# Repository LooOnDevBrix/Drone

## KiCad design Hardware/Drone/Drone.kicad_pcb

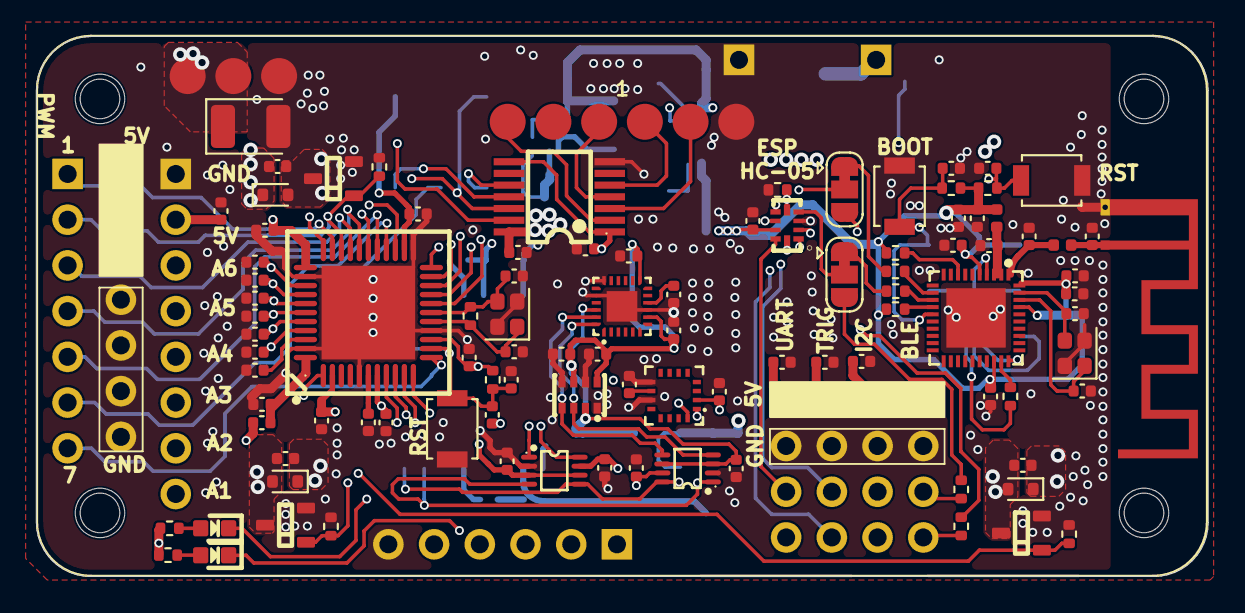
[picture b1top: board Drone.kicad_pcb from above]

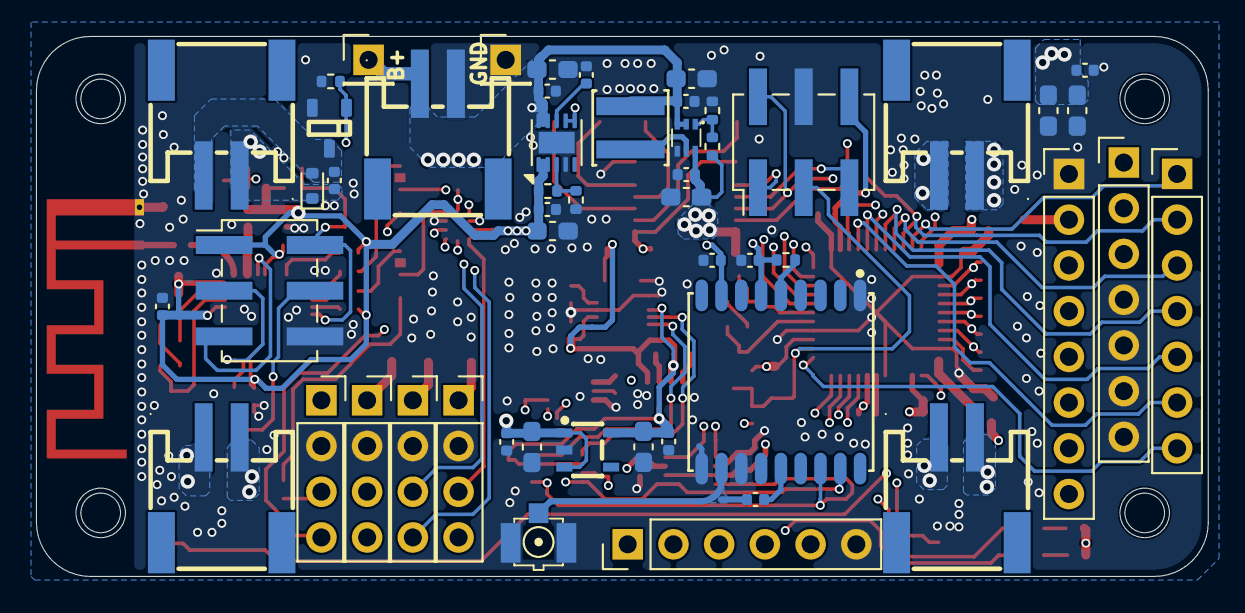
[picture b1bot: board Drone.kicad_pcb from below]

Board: 4 copper layers, 65.1 x 30.0 mm, 164 parts (52 on the bottom side), 85 nets.

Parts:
A1: RASPBERRYPI-ZERO; RASPBERRYPI-ZERO_RPI-ZERO
C1, C2, C18, C22, C26, C29, C32, C34: 10uF; C_0603_1608Metric_Pad1.08x0.95mm_HandSolder
C3, C6, C7, C8, C9, C10, C11, C13, C14, C15, C17, C19, C20, C21, C24, C25, C28, C30, C31, C33, C35, C38, C40, C42, C43, C44, C46, C47, C48, C49, C50, C51, C53, C54, C55, C56, C59, C60, C62, C63, C64, C66, C71, C75, C76, C77, C78: 100nF; C_0402_1005Metric
C4, C5, C12, C74: 10uF; C_0402_1005Metric
C16, C41: 4.7uF; C_0402_1005Metric
C23: 100uF; CP_EIA-3528-12_Kemet-T
C27, C61: TBD; C_0402_1005Metric
C36, C37: 12pF; C_0402_1005Metric
C39, C45, C65, C72: 1uF; C_0402_1005Metric
C69, C70: 10pF; C_0402_1005Metric
C73: 10nF; C_0402_1005Metric
D1, D2, D3, D4: 1N4148WT; D_SOD-523
H1, H2, H3, H4: MountingHole; MountingHole_2.2mm_M2
J1: HC-05; PinSocket_1x04_P2.54mm_Vertical
J2, J15: Conn_01x06; PinHeader_2x03_P2.54mm_Vertical_SMD
J3: Screw_Terminal_01x08; PinHeader_1x08_P2.54mm_Vertical
J4: BAT; CONN-SMD_P2.00_S2B-PH-SM4-TB-LF-SN
J5: FTDT; PinHeader_1x06_P2.54mm_Vertical
J7, J9: Conn_01x07; PinHeader_1x07_P2.54mm_Vertical
J10: DC1; CONN-SMD_P2.00_S2B-PH-SM4-TB-LF-SN
J11: HC-SRF05; PinSocket_1x04_P2.54mm_Vertical
J12: PMW3901; PinSocket_1x04_P2.54mm_Vertical
J14: I2C; PinSocket_1x04_P2.54mm_Vertical
J16: DC2; CONN-SMD_P2.00_S2B-PH-SM4-TB-LF-SN
J17: DC3; CONN-SMD_P2.00_S2B-PH-SM4-TB-LF-SN
J18: DC4; CONN-SMD_P2.00_S2B-PH-SM4-TB-LF-SN
JP1, JP2: Jumper_3_Bridged12; SolderJumper-3_P1.3mm_Bridged12_RoundedPad1.0x1.5mm
L1: 1uH/XEL4030-102ME; IND-SMD_L4.0-W4.0-A
L2: 10uH; C_0402_1005Metric
L3: 47nH; C_0402_1005Metric
L4: 0R; L_0402_1005Metric
L5: 20nH; L_0402_1005Metric
LE2, LE4: RED/0603; LED_0603
Q1, Q2, Q3, Q4: SI2300; SOT23-3
R1, R8, R22, R23: 100R; R_0402_1005Metric
R2: 1.15K; R_0402_1005Metric
R3, R4, R5, R9, R15, R17, R18, R20, R21, R24: 10K; R_0402_1005Metric
R6: 100K; R_0402_1005Metric
R7: 3.57K; R_0402_1005Metric
R10, R11: 220R; R_0402_1005Metric
R12: 470R; R_0402_1005Metric
R13: 4K7; R_0402_1005Metric
R14: 1K; R_0402_1005Metric
R16: 732K; R_0402_1005Metric
SW1, SW2, SW3: SW_Push; SW_SPST_B3U-1000P
TP1, TP2, TP3, TP28, TP29, TP30, TP31, TP32, TP33: TestPoint; CONN-SMD_YTC1P-3015-01
TP41, TP42: TestPoint; PinHeader_1x01_P2.54mm_Vertical
U1: ICM-20948; QFN-24_L3.0-W3.0-P0.40-BL-EP
U2: QMC5883P; LGA-16_L3.0-W3.0-P0.50-BL_SQ
U3: BMP280; LGA-8_L2.5-W2.0-P0.65_AMP6127
U4: ATMEGA32U4-MU; VQFN-44_L7.0-W7.0-P0.50-BL-EP5.2
U5: TS5A23159RSER; UQFN-10_L2.0-W1.5-P0.50-BL-EP
U6: TPS61023DRLR; SOT-563_L1.6-W1.2-P0.50-LS1.6-BR
U7: TPS7A91; Texas_S-PDSO-N10_EP1.2x2mm
U8: ESP32-C6_C5364646; QFN-40_L5.0-W5.0-P0.40-TL-EP3.3
U9, U10: TCA9406DCUR; VSSOP-8_L2.3-W2.0-P0.50-LS3.1-BL
U11: ATGM336H-5N31; GPSM-SMD_ATGM336H-TR
U12: TXB0104QPWRQ1; TSSOP-14_L5.0-W4.4-P0.65-LS6.4-BL
U13: Ipex; IPEX_Antena_Connector
U16: AP2112K-1_8TRG1; SOT-25_L3.0-W1.6-P0.95-LS2.8-BL
U17: Texas_SWRA117D_2.4GHz_Right
Y1: 16Mhz; Crystal_SMD_2016-4Pin_2.0x1.6mm
Y3: 40MHz; Crystal_SMD_2016-4Pin_2.0x1.6mm

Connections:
+1.8V: C13.1, C14.1, C17.1, C19.1, C34.1, C35.1, C46.1, U1.8 (VDDIO), U1.13 (VDD), U1.22 (nCS), U3.2 (CSB), U3.6 (VDDIO), U3.8 (VDD), U9.3 (VCCA), U9.6 (OE), U16.5 (VOUT)
+3.3V: C15.1, C29.1, C30.1, C47.1, C48.1, C50.1, C55.1, C56.1, C65.1, C71.1, C72.1, C73.1, C74.1, C75.1, C77.1, C78.1, J2.1, L5.2, R3.1, R4.1, R7.2, R9.1, R13.1, R24.1, U2.2 (VDD), U5.8 (VCC), U7.1 (OUT), U7.2 (OUT), U8.5 (VDDPST1), U8.28 (VDDPST2), U8.37 (VDDA1), U8.40 (VDDA2), U9.7 (VCCB), U10.3 (VCCA), U10.6 (OE), U11.6 (VBAT), U11.8 (VCC), U12.1 (VCCA), U12.8 (OE)
+3.7BAT: C2.1, C24.1, C26.1, C28.1, C32.1, C33.1, C60.1, C62.1, C63.1, C64.1, D1.1 (K), D2.1 (K), D3.1 (K), D4.1 (K), J4.1, J10.1, J16.1, J17.1, J18.1, L1.1, TP41.1, U6.2 (EN), U6.3 (VIN), U7.6 (SS_CTRL), U7.7 (EN), U7.9 (IN), U7.10 (IN), U16.1 (VIN), U16.3 (EN)
+5V: A1.2 (5V[1]), A1.4 (5V[2]), C1.1, C5.1, C12.2, C18.1, C21.1, C22.1, C23.1, C25.1, C38.1, C40.2, C43.2, C44.2, C45.1, C49.1, C51.1, C59.1, C66.1, J1.1, J3.2, J5.4, J7.1, J7.2, J7.3, J11.1, J12.1, J14.1, J15.6, L2.2, R10.1, R11.1, R15.1, R16.2, TP1.1, TP2.1, U4.2 (UVcc), U4.7 (VBus), U4.14 (VCC), U4.24 (AVCC), U4.34 (VCC), U6.6 (VOUT), U10.7 (VCCB), U12.14 (VCCB)
/MFC/3V3.SCL: U2.16 (SDA), U9.8 (SCL_B), U10.5 (SCL_A), U11.17 (SCL)
/MFC/3V3.SDA: U2.1 (SCK), U9.1 (SDA_B), U10.4 (SDA_A), U11.16 (SDA)
/MFC/5V.SCL: J14.3, U4.18 (PD0(OC0B/SCL/INT0)), U10.8 (SCL_B)
/MFC/5V.SDA: J14.4, U4.19 (PD1(SDA/INT1)), U10.1 (SDA_B)
/MFC/A1: C11.1, J3.8, U4.41 (PF0(ADC0))
/MFC/A2: C10.1, J3.7, U4.40 (PF1(ADC1))
/MFC/A3: C9.1, J3.6, U4.39 (PF4(ADC4/TCK))
/MFC/A4: C8.1, J3.5, U4.38 (PF5(ADC5/TMS))
/MFC/A5: C7.1, J3.4, U4.37 (PF6(ADC6/TDO))
/MFC/A6: C6.1, J3.3, U4.36 (PF7(ADC7/TDI))
/MFC/CHOOSE: R18.2, U4.1 (PE6(INT.6/AIN0)), U5.1 (IN1), U5.5 (IN2)
/MFC/DTR: C54.1, J5.1
/MFC/ECHO: J11.4, U4.33 (PE2(HWB#))
/MFC/PMW3901_RX: J12.3, U5.9 (NC1)
/MFC/PMW3901_TX: J12.4, U5.7 (NC2)
/MFC/PWM1: J9.1, Q1.1 (G), R5.1, U4.32 (PC7(ICP3/CLK0/OC4A))
/MFC/PWM2: J9.2, Q2.1 (G), R17.1, U4.31 (PC6(OC3A/OC4A#))
/MFC/PWM3: J9.3, Q3.1 (G), R20.1, U4.30 (PB6(PCINT6/OC1B/OC4B/ADC13))
/MFC/PWM4: J9.4, Q4.1 (G), R21.1, U4.29 (PB5(PCINT5/OC1A/OC4B#/ADC12))
/MFC/PWM5: J9.5, U4.27 (PD7(T0/OC4D/ADC10))
/MFC/PWM6: J9.6, U4.26 (PD6(T1/OC4D#/ADC9))
/MFC/PWM7: J9.7, U4.12 (PB7(PCINT7/OC0A/OC1C/RTS#))
/MFC/RST: C53.1, C54.2, J15.3, R15.2, SW3.2, U4.13 (RESET#)
/MFC/RXD1: J5.2, U4.20 (PD2(RXD1/INT2)), U5.10 (COM1)
/MFC/TRIG: J11.3, U4.28 (PB4(PCINT4/ADC11))
/MFC/TXD1: J5.3, U4.21 (PD3(TXD1/INT3)), U5.6 (COM2)
/MFC/U4.CS: U4.8 (PB0(SS/PCINT0)), U12.13 (B1)
/MFC/U4.MISO: J15.1, U4.11 (PB3(PDO/PCINT3/MISO)), U12.10 (B4)
/MFC/U4.MOSI: J15.5, U4.10 (PB2(PDI/PCINT2/MOSI)), U12.11 (B3)
/MFC/U4.SCK: J15.2, U4.9 (PB1(PCINT1/SCLK)), U12.12 (B2)
/MFC/UART_RX: JP1.2 (C), U5.2 (NO1)
/MFC/UART_TX: JP2.2 (C), U5.4 (NO2)
/MFC/pi.CS: A1.15 (GPIO22/GEN3), TP28.1, U12.2 (A1)
/MFC/pi.MISO: A1.21 (GPIO9/MISO), TP31.1, U12.5 (A4)
/MFC/pi.MOSI: A1.19 (GPIO10/MOSI), TP30.1, U12.4 (A3)
/MFC/pi.SCK: A1.23 (GPIO11/SCLK), TP32.1, U12.3 (A2)
/RC Control/DC1L: C60.2, D1.2 (A), J10.2, Q1.3 (D)
/RC Control/DC2L: C62.2, D2.2 (A), J16.2, Q2.3 (D)
/RC Control/DC3L: C63.2, D3.2 (A), J17.2, Q3.3 (D)
/RC Control/DC4L: C64.2, D4.2 (A), J18.2, Q4.3 (D)
/Sensor/1V8.SCL: U1.23 (SCL/SCLK), U3.4 (SCK), U9.5 (SCL_A)
/Sensor/1V8.SDA: U1.24 (SDA/SDI), U3.3 (SDI), U9.4 (SDA_A)
/Sensor/Rfa: L3.2, U11.11 (RF_IN), U13.1
/Wireless/BOOT: C3.1, J2.2, R3.2, SW1.1, U8.15 (GPIO9)
/Wireless/ESP_RST: C4.1, J2.5, R4.2, SW2.2, U8.4 (CHIP_PU)
/Wireless/ESP_RX: J2.3, U8.30 (U0RXD)
/Wireless/ESP_TX: J2.4, R12.2
/Wireless/RX_ESP: JP2.1 (A), R23.2
/Wireless/RX_HC05: JP2.3 (B), R8.2
/Wireless/TX_ESP: JP1.1 (A), R22.2
/Wireless/TX_HC05: JP1.3 (B), R1.2
GND: A1.6 (GND[8]), A1.25 (GND[2]), C1.2, C2.2, C3.2, C4.2, C5.2, C6.2, C7.2, C8.2, C9.2, C10.2, C11.2, C12.1, C13.2, C14.2, C15.2, C16.2, C17.2, C18.2, C19.2, C20.2, C21.2, C22.2, C23.2, C24.2, C25.2, C26.2, C27.2, C28.2, C29.2, C30.2, C31.2, C32.2, C33.2, C34.2, C35.2, C36.2, C37.2, C38.2, C39.2, C40.1, C41.1, C42.1, C43.1, C44.1, C45.2, C46.2, C47.2, C48.2, C49.2, C50.2, C51.2, C53.2, C55.2, C56.2, C59.2, C61.2, C65.2, C66.2, C69.2, C70.2, C71.2, C72.2, C73.2, C74.2, C75.2, C76.2, C77.2, C78.2, J1.2, J2.6, J3.1, J4.2, J5.6, J7.4, J7.5, J7.6, J7.7, J11.2, J12.2, J14.2, J15.4, Q1.2 (S), Q2.2 (S), Q3.2 (S), Q4.2 (S), R2.1, R5.2, R6.1, R17.2, R18.1, R20.2, R21.2, SW1.2, SW2.1, SW3.1, TP3.1, TP33.1, TP42.1, U1.9 (SDO/AD0), U1.18 (GND), U1.20 (RESV), U1.25 (EP), U2.9 (GND), U2.11 (GND), U3.1 (GND), U3.5 (SDO), U3.7 (GND), U4.5 (UGnd), U4.15 (GND), U4.23 (GND), U4.35 (GND), U4.43 (GND), U4.45 (EP), U5.3 (GND), U6.4 (GND), U7.4 (GND), U7.11 (GND), U8.41 (EP), U9.2 (GND), U10.2 (GND), U11.1 (GND), U11.10 (GND), U11.12 (GND), U12.7 (GND), U13.2, U16.2 (GND), U17.2, Y1.2, Y1.4, Y3.2, Y3.4
unnamed: C27.1, L4.2, U17.1
unnamed: C42.2, L2.1, U4.44 (AVCC)
unnamed: C76.1, L5.1, U8.2 (VDDA3P3), U8.3 (VDDA3P3)
unnamed: J1.3, R8.1
unnamed: J1.4, R1.1
unnamed: LE2.1, R11.2
unnamed: LE4.1, R10.2
unnamed: C20.1, U1.10 (REGOUT)
unnamed: C16.1, U2.10 (C1)
unnamed: C41.2, U4.42 (AREF)
unnamed: LE2.2, U4.25 (PD4(ICP1/ADC8))
unnamed: LE4.2, U4.22 (PD5(XCK1/CTS#))
unnamed: C39.1, U4.6 (UCap)
unnamed: C37.1, R14.2, U4.17 (XTAL1), Y1.3
unnamed: C36.1, R14.1, U4.16 (XTAL2), Y1.1
unnamed: R6.2, R16.1, U6.1 (FB)
unnamed: L1.2, U6.5 (SW)
unnamed: R2.2, R7.1, U7.3 (FB)
unnamed: C31.1, U7.8 (NR/SS)
unnamed: C61.1, L4.1, U8.1 (ANT)
unnamed: R24.2, U8.8 (GPIO2)
unnamed: R13.2, U8.14 (GPIO8)
unnamed: R22.1, U8.12 (MTCK)
unnamed: R23.1, U8.13 (MTDO)
unnamed: R12.1, U8.29 (U0TXD)
unnamed: C69.1, U8.38 (XTAL_N), Y3.1
unnamed: C70.1, U8.39 (XTAL_P), Y3.3
unnamed: R9.2, U11.5 (ON/OFF)
unnamed: L3.1, U11.14 (VCC_RF)

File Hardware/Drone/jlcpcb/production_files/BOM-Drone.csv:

"Reference","Qty","Value","Footprint","JLC Part"
"C1,C2,C18,C22,C26,C29,C32,C34","8","10uF","Capacitor_SMD:C_0603_1608Metric_Pad1.08x0.95mm_HandSolder","C1691"
"C3,C6,C7,C8,C9,C10,C11,C13,C14,C15,C17,C19,C20,C21,C24,C25,C28,C30,C31,C33,C35,C38,C40,C42,C43,C44,C46,C47,C48,C49,C50,C51,C53,C54,C55,C56,C59,C60,C62,C63,C64,C66,C71,C75,C76,C77,C78","47","100nF","Capacitor_SMD:C_0402_1005Metric","C1525"
"C4,C5,C12,C74","4","10uF","Capacitor_SMD:C_0402_1005Metric","C15525"
"C16,C41","2","4.7uF","Capacitor_SMD:C_0402_1005Metric","C23733"
"C23","1","100uF","Capacitor_Tantalum_SMD:CP_EIA-3528-12_Kemet-T","C140381"
"C36,C37","2","12pF","Capacitor_SMD:C_0402_1005Metric","C26406"
"C39,C45,C65,C72","4","1uF","Capacitor_SMD:C_0402_1005Metric","C14445"
"C69,C70","2","10pF","Capacitor_SMD:C_0402_1005Metric","C1634"
"C73","1","10nF","Capacitor_SMD:C_0402_1005Metric","C57112"
"D1,D2,D3,D4","4","1N4148WT","Diode_SMD:D_SOD-523","C68948"
"J1","1","HC-05","Connector_PinSocket_2.54mm:PinSocket_1x04_P2.54mm_Vertical","C2691448"
"J2,J15","2","Conn_01x06","Connector_PinHeader_2.54mm:PinHeader_2x03_P2.54mm_Vertical_SMD","C3294461"
"J4","1","BAT","Library:CONN-SMD_P2.00_S2B-PH-SM4-TB-LF-SN","C295747"
"J5","1","FTDT","Connector_PinHeader_2.54mm:PinHeader_1x06_P2.54mm_Vertical","C492405"
"J10","1","DC1","Library:CONN-SMD_P2.00_S2B-PH-SM4-TB-LF-SN","C295747"
"J11","1","HC-SRF05","Connector_PinSocket_2.54mm:PinSocket_1x04_P2.54mm_Vertical","C2691448"
"J12","1","PMW3901","Connector_PinSocket_2.54mm:PinSocket_1x04_P2.54mm_Vertical","C2691448"
"J14","1","I2C","Connector_PinSocket_2.54mm:PinSocket_1x04_P2.54mm_Vertical","C2691448"
"J16","1","DC2","Library:CONN-SMD_P2.00_S2B-PH-SM4-TB-LF-SN","C295747"
"J17","1","DC3","Library:CONN-SMD_P2.00_S2B-PH-SM4-TB-LF-SN","C295747"
"J18","1","DC4","Library:CONN-SMD_P2.00_S2B-PH-SM4-TB-LF-SN","C295747"
"L1","1","1uH/XEL4030-102ME","Library:IND-SMD_L4.0-W4.0-A","C5441341"
"L2","1","10uH","Capacitor_SMD:C_0402_1005Metric","C910650"
"L3","1","47nH","Capacitor_SMD:C_0402_1005Metric","C22334"
"L4","1","0R","Inductor_SMD:L_0402_1005Metric","C122704"
"L5","1","20nH","Inductor_SMD:L_0402_1005Metric","C77124"
"LE2,LE4","2","RED/0603","IVS_FOOTPRINTS:LED_0603","C2286"
"Q1,Q2,Q3,Q4","4","SI2300","IVS_FOOTPRINTS:SOT23-3","C72271"
"R1,R8,R22,R23","4","100R","Resistor_SMD:R_0402_1005Metric","C25076"
"R2","1","1.15K","Library:R_0402_1005Metric","C29401"
"R3,R4,R5,R9,R15,R17,R18,R20,R21","9","10K","Resistor_SMD:R_0402_1005Metric","C25744"
"R6","1","100K","Library:R_0402_1005Metric","C25530"
"R7","1","3.57K","Library:R_0402_1005Metric","C137991"
"R10,R11","2","220R","Resistor_SMD:R_0402_1005Metric","C25091"
"R12","1","470R","Resistor_SMD:R_0402_1005Metric","C25167"
"R13","1","4K7","Resistor_SMD:R_0402_1005Metric","C25900"
"R14","1","1K","Resistor_SMD:R_0402_1005Metric","C11702"
"R16","1","732K","Library:R_0402_1005Metric","C27016"
"SW1,SW2,SW3","3","SW_Push","Button_Switch_SMD:SW_SPST_B3U-1000P","C231329"
"TP1,TP2,TP3,TP28,TP29,TP30,TP31,TP32,TP33","9","TestPoint","Library:CONN-SMD_YTC1P-3015-01","C5221293"
"TP41,TP42","2","TestPoint","Connector_PinHeader_2.54mm:PinHeader_1x01_P2.54mm_Vertical","C492400"
"U1","1","ICM-20948","Library:QFN-24_L3.0-W3.0-P0.40-BL-EP","C726001"
"U2","1","QMC5883P","Library:LGA-16_L3.0-W3.0-P0.50-BL_SQ","C2847467"
"U3","1","BMP280","Library:LGA-8_L2.5-W2.0-P0.65_AMP6127","C83291"
"U4","1","ATMEGA32U4-MU","Library:VQFN-44_L7.0-W7.0-P0.50-BL-EP5.2","C112161"
"U5","1","TS5A23159RSER","Library:UQFN-10_L2.0-W1.5-P0.50-BL-EP","C138710"
"U6","1","TPS61023DRLR","Library:SOT-563_L1.6-W1.2-P0.50-LS1.6-BR","C919459"
"U7","1","TPS7A91","Package_DFN_QFN:Texas_S-PDSO-N10_EP1.2x2mm","C2878140"
"U8","1","ESP32-C6_C5364646","Library:QFN-40_L5.0-W5.0-P0.40-TL-EP3.3","C5364646"
"U9,U10","2","TCA9406DCUR","Library:VSSOP-8_L2.3-W2.0-P0.50-LS3.1-BL","C840107"
"U11","1","ATGM336H-5N31","Library:GPSM-SMD_ATGM336H-TR","C90770"
"U12","1","TXB0104QPWRQ1","Library:TSSOP-14_L5.0-W4.4-P0.65-LS6.4-BL","C527571"
"U13","1","Ipex","IVS_FOOTPRINTS:IPEX_Antena_Connector","C2987682"
"U16","1","AP2112K-1_8TRG1","Library:SOT-25_L3.0-W1.6-P0.95-LS2.8-BL","C176944"
"Y1","1","16Mhz","Crystal:Crystal_SMD_2016-4Pin_2.0x1.6mm","C2682778"
"Y3","1","40MHz","Crystal:Crystal_SMD_2016-4Pin_2.0x1.6mm","C20885029"

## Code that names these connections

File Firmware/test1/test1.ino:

#include <QMC5883LCompass.h>
#include <Wire.h>

QMC5883LCompass compass;

// #define LED_PIN 4  
// #define LED_PIN2 5  

// int pwmPins[] = {6, 7}; 

void setup() {
  // Define UART
  Serial1.begin(9600);

  //Define I2C
  Wire.begin();
  
//   //Define PIN OUT
//   pinMode(LED_PIN, OUTPUT);
//   pinMode(LED_PIN2, OUTPUT); 

//   //Define PWM
//   for (int i = 0; i < 2; i++) {
//     pinMode(pwmPins[i], OUTPUT);
//   }

    // ====== PC7 (OC4A, Timer4) ======
    // DDRC |= (1 << PC7);                 // PC7 output
    // TCCR4A = (1 << COM4A1) | (1 << PWM4A); // Fast PWM, non-inverting
    // TCCR4B = (1 << CS41);               // prescaler = 8
    // OCR4A = 128;                        // duty 50%

    // // ====== PC6 (OC3A, Timer3) ======
    // DDRC |= (1 << PC6);                 // PC6 output
    // TCCR3A = (1 << COM3A1) | (1 << WGM30); // Fast PWM 8-bit
    // TCCR3B = (1 << WGM32) | (1 << CS31);   // prescaler = 8
    // OCR3A = 128;                        // duty 50%

    // // ====== PB6 (OC1B, Timer1) ======
    // DDRB |= (1 << PB6);                 // PB6 output
    // TCCR1A = (1 << COM1B1) | (1 << WGM10); // Fast PWM 8-bit
    // TCCR1B = (1 << WGM12) | (1 << CS11);   // prescaler = 8
    // OCR1B = 128;                        // duty 50%

    // // ====== PB5 (OC1A, Timer1) ======
    // DDRB |= (1 << PB5);                 // PB5 output
    // TCCR1A |= (1 << COM1A1);               // bật OC1A
    // OCR1A = 128;                        // duty 50%

    // compass.init();
}

void loop() {

  //   //TEST UART
  Serial1.println("I2C Scanner");

//   // TEST LED
//   // digitalWrite(LED_PIN, HIGH);  // bật LED
//   // digitalWrite(LED_PIN2, LOW);  // bật LED
//   // delay(500);
//   // digitalWrite(LED_PIN, LOW);   // tắt LED
//   // digitalWrite(LED_PIN2, HIGH);  // bật LED
//   // delay(500);

//   //TEST PWM
//   //   analogWrite(9, 64);   // ~25%
//   // analogWrite(10, 128); // ~50%
//   // analogWrite(5, 192);  // ~75%
//   // analogWrite(13, 255); // 100% (ON)
//   // analogWrite(12, 32);  // ~12%
//   // analogWrite(6, 160);  // ~62%
//   // analogWrite(11, 96);  // ~37%
//   for(int i = 0; i < 2; i++){
//     for(int j = 0; j < 255; j++){
//         analogWrite(pwmPins[i], j);
//         delay(1000);
//       }
//   }

  // for (int val = 254; val < 255; val++) {
  //   OCR4A = val;  // PC7
  //   OCR3A = val;  // PC6
  //   OCR1A = val;  // PB5
  //   OCR1B = val;  // PB6
  //   delay(10);
  // }

    int x, y, z;
  
  byte error, address;
  int nDevices = 0;

  for (address = 1; address < 255; address++) {
    Wire.beginTransmission(address);
    error = Wire.endTransmission();

    if (error == 0) {
      Serial1.print("I2C device found at 0x");
      Serial1.println(address, HEX);
      nDevices++;
    }

  }

  if (nDevices == 0) {
    Serial1.println("No I2C devices found\n");
  }
  
  delay(100);
}

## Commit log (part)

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2025-09-14 add first project
